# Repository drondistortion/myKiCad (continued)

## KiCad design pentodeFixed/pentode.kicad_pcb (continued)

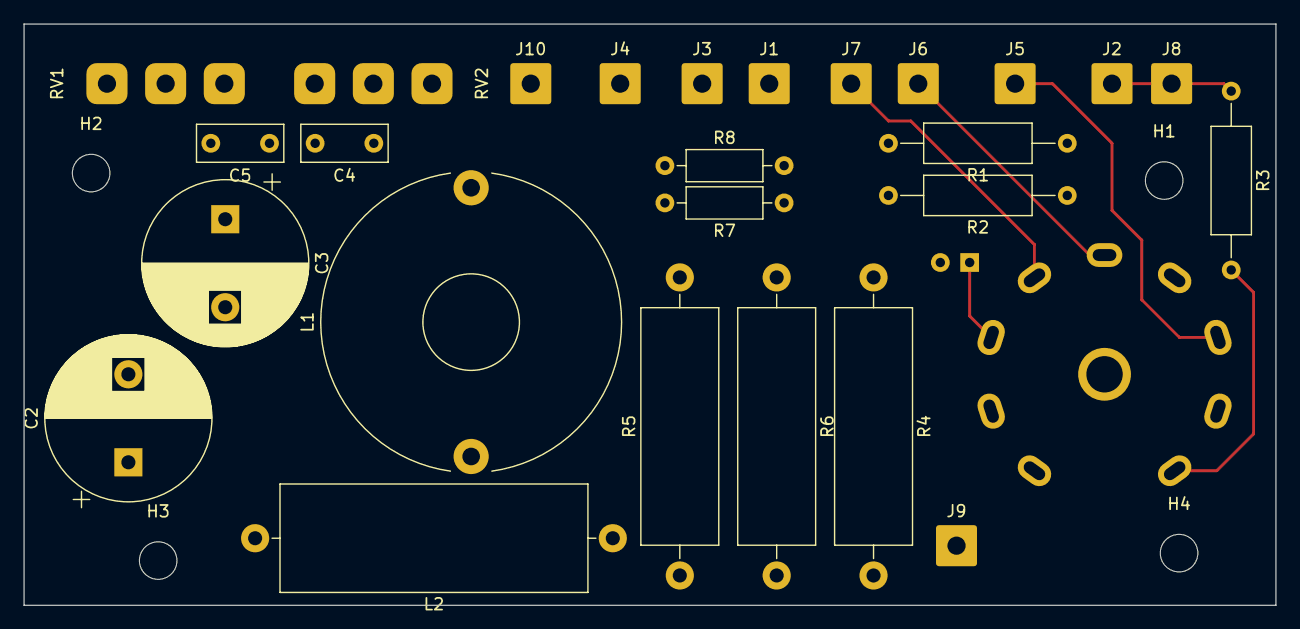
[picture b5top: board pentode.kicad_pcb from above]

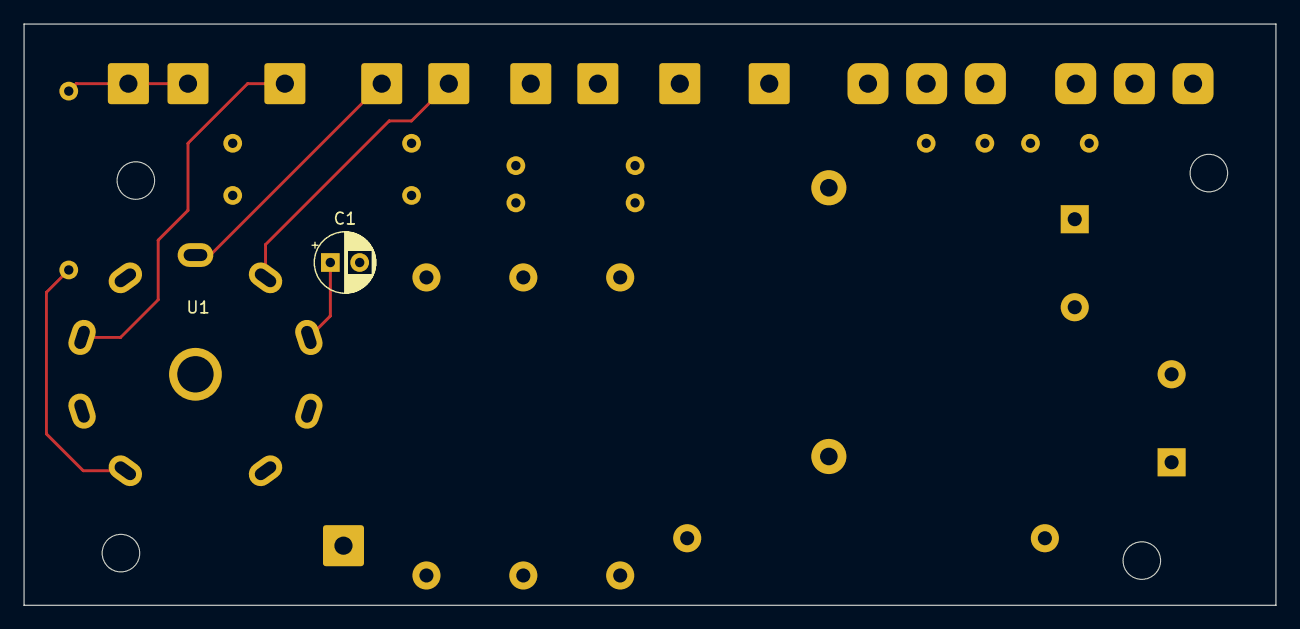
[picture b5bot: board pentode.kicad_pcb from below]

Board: 2 copper layers, 106.7 x 49.5 mm, 32 parts (2 on the bottom side), 15 nets.

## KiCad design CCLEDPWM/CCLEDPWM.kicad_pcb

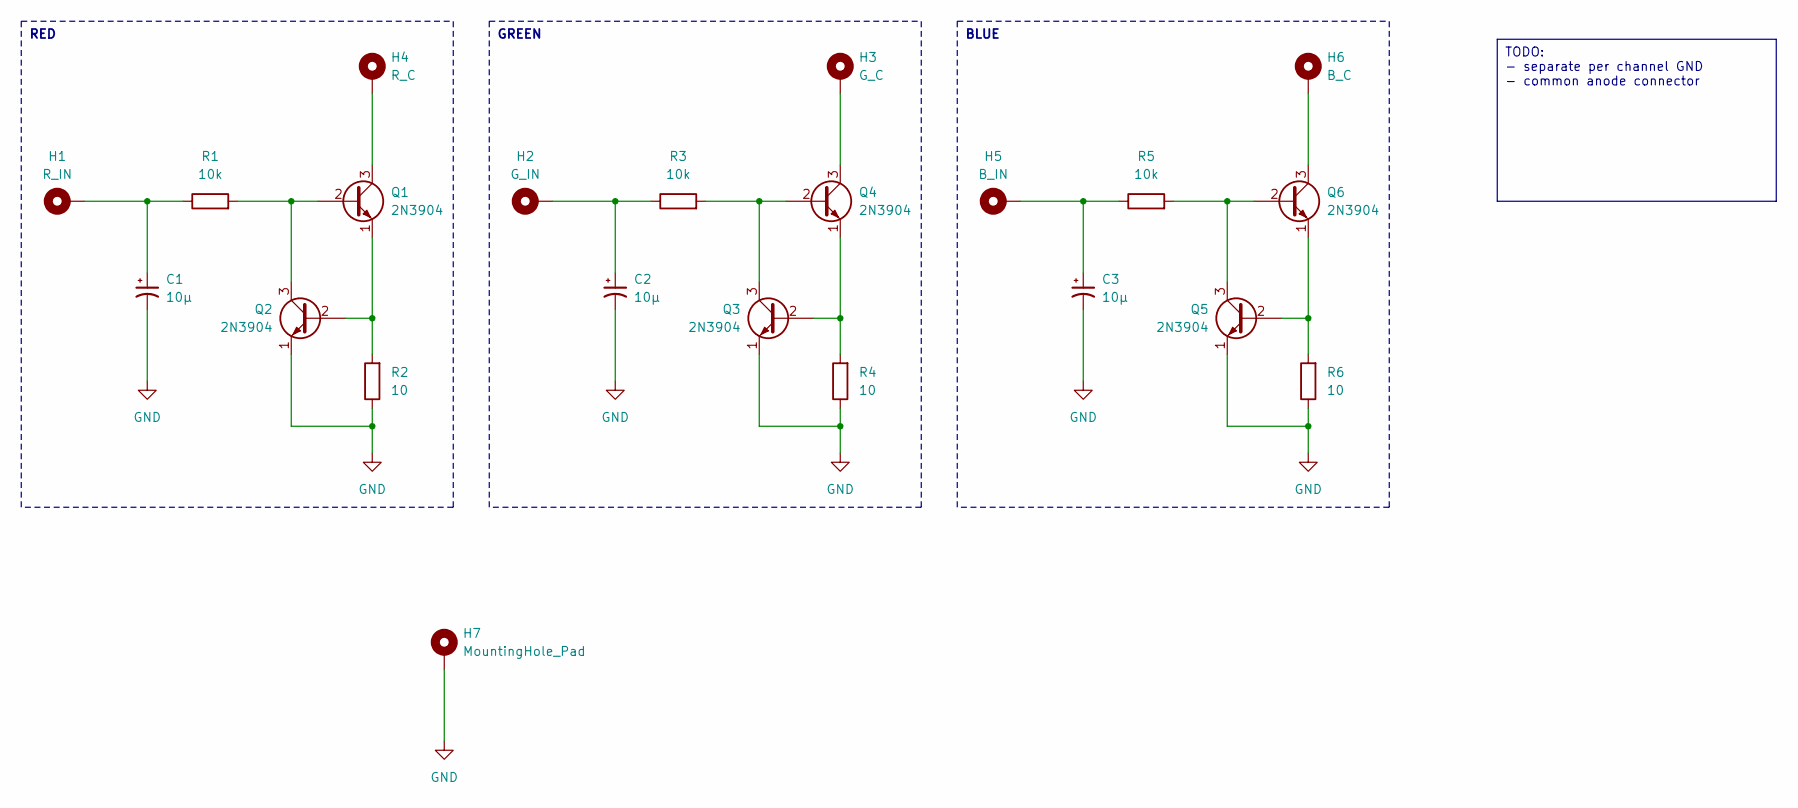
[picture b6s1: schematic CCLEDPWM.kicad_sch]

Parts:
C1, C2, C3: 10µ; CP_Radial_D5.0mm_P2.50mm
H1: R_IN; MountingHole_2.7mm_Pad
H2: G_IN; MountingHole_2.7mm_Pad
H3: G_C; MountingHole_2.7mm_Pad
H4: R_C; MountingHole_2.7mm_Pad
H5: B_IN; MountingHole_2.7mm_Pad
H6: B_C; MountingHole_2.7mm_Pad
H7: MountingHole_Pad; MountingHole_2.7mm_Pad
Q1, Q2, Q3, Q4, Q5, Q6: 2N3904; TO-92_Inline_Wide
R1, R3, R5: 10k; R_Axial_DIN0204_L3.6mm_D1.6mm_P7.62mm_Horizontal
R2, R4, R6: 10; R_Axial_DIN0204_L3.6mm_D1.6mm_P7.62mm_Horizontal

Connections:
GND: C1.2, C2.2, C3.2, H7.1, Q2.1 (E), Q3.1 (E), Q5.1 (E), R2.1, R4.1, R6.1
unnamed: C1.1, H1.1, R1.1
unnamed: C2.1, H2.1, R3.1
unnamed: C3.1, H5.1, R5.1
unnamed: Q1.2 (B), Q2.3 (C), R1.2
unnamed: H4.1, Q1.3 (C)
unnamed: Q1.1 (E), Q2.2 (B), R2.2
unnamed: Q3.2 (B), Q4.1 (E), R4.2
unnamed: Q3.3 (C), Q4.2 (B), R3.2
unnamed: H3.1, Q4.3 (C)
unnamed: Q5.2 (B), Q6.1 (E), R6.2
unnamed: Q5.3 (C), Q6.2 (B), R5.2
unnamed: H6.1, Q6.3 (C)

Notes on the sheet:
TODO: - separate per channel GND - common anode connector
GREEN
BLUE
RED

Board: 2 copper layers, 22 parts (0 on the bottom side), 13 nets, no tracks yet.

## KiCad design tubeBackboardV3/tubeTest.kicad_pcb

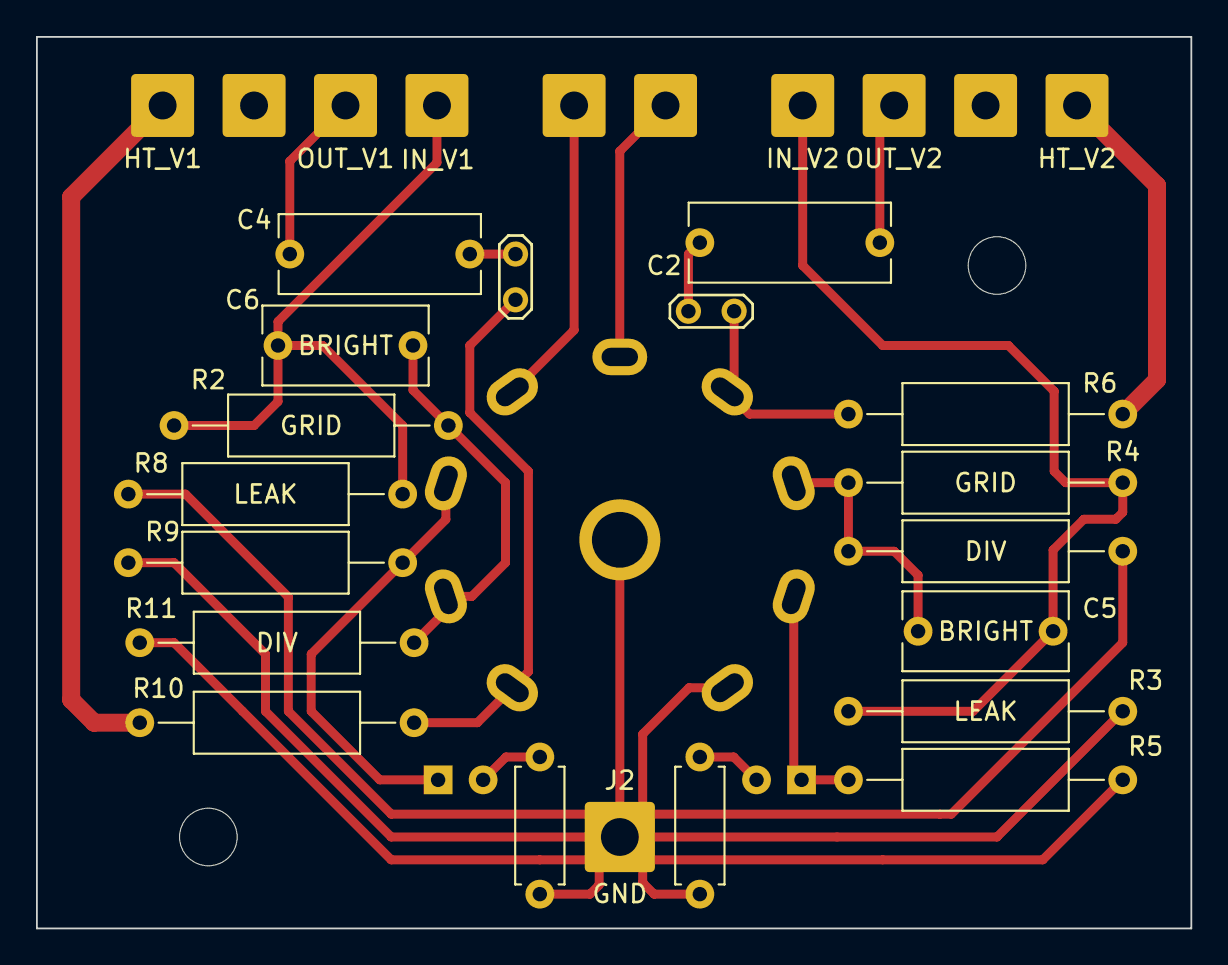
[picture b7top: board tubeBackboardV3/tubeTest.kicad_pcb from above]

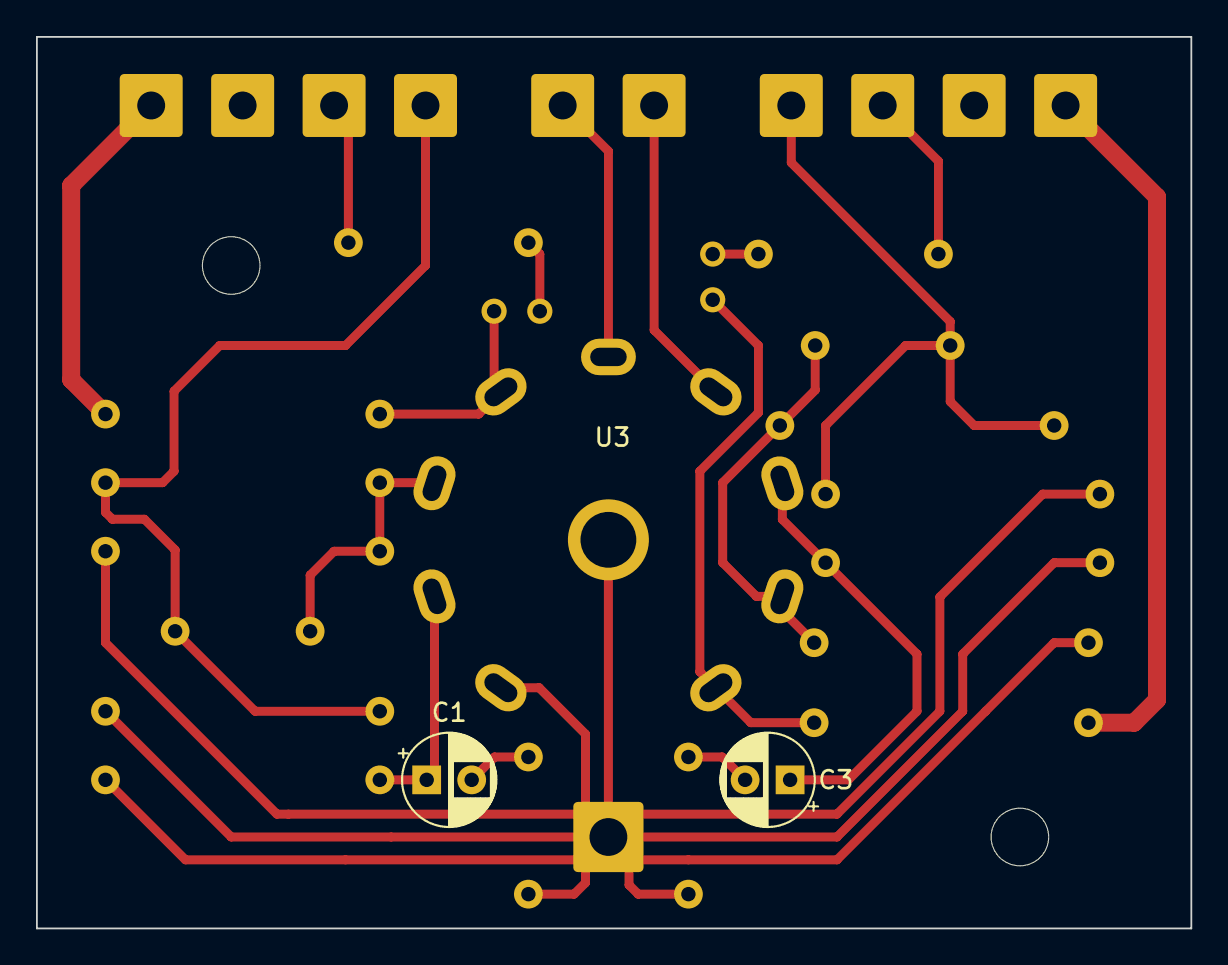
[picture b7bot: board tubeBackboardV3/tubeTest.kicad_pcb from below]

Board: 2 copper layers, 64.1 x 49.5 mm, 34 parts (3 on the bottom side), 19 nets.

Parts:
C1: 0.1µF; CP_Radial_D5.0mm_P2.50mm
C2, C4: 22n; C_Rect_L11.0mm_W4.2mm_P10.00mm_MKT
C3: 1µF; CP_Radial_D5.0mm_P2.50mm
C5, C6: BRIGHT; C_Rect_L9.0mm_W4.2mm_P7.50mm_MKT
H1, H2: MountingHole; MountingHole_3.2mm_M3
J1: IN_V2; SolderWire-0.75sqmm_1x01_D1.25mm_OD3.5mm
J2: GND; SolderWire-1.5sqmm_1x01_D1.7mm_OD3.9mm
J3, J6: ACFIL; SolderWire-0.75sqmm_1x01_D1.25mm_OD3.5mm
J4, J11: BL; SolderWire-0.75sqmm_1x01_D1.25mm_OD3.5mm
J5: OUT_V1; SolderWire-0.75sqmm_1x01_D1.25mm_OD3.5mm
J7: IN_V1; SolderWire-0.75sqmm_1x01_D1.25mm_OD3.5mm
J8: OUT_V2; SolderWire-0.75sqmm_1x01_D1.25mm_OD3.5mm
J9: HT_V2; SolderWire-0.75sqmm_1x01_D1.25mm_OD3.5mm
J10: HT_V1; SolderWire-0.75sqmm_1x01_D1.25mm_OD3.5mm
R1, R11: DIV; R_Axial_DIN0309_L9.0mm_D3.2mm_P15.24mm_Horizontal
R2, R4: GRID; R_Axial_DIN0309_L9.0mm_D3.2mm_P15.24mm_Horizontal
R3, R8: LEAK; R_Axial_DIN0309_L9.0mm_D3.2mm_P15.24mm_Horizontal
R5, R9: 1.8K; R_Axial_DIN0309_L9.0mm_D3.2mm_P15.24mm_Horizontal
R6, R10: 220K; R_Axial_DIN0309_L9.0mm_D3.2mm_P15.24mm_Horizontal
R7, R12: 100; R_Axial_DIN0207_L6.3mm_D2.5mm_P7.62mm_Horizontal
TP3, TP4: TestPoint_2Pole; TestPoint_2Pads_Pitch2.54mm_Drill0.8mm
U3: ECC83; Valve_6N2P

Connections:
+3V0: J6.1, U3.5 (F1)
-3V3: J3.1, U3.4 (F1)
GND: J2.1, R1.1, R3.2, R5.2, R7.2, R8.1, R9.2, R11.1, R12.2, U3.9 (F2)
unnamed: C1.2, R7.1
unnamed: C2.1, TP3.1
unnamed: C3.2, R12.1
unnamed: C4.1, TP4.1
unnamed: C5.1, J1.1, R3.1, R4.1
unnamed: C4.2, J5.1
unnamed: C6.1, J7.1, R2.1, R8.2
unnamed: C2.2, J8.1
unnamed: J9.1, R6.1
unnamed: J10.1, R10.1
unnamed: R6.2, TP3.2, U3.6 (A)
unnamed: C5.2, R1.2, R4.2, U3.7 (G)
unnamed: C1.1, R5.1, U3.8 (K)
unnamed: R10.2, TP4.2, U3.1 (A)
unnamed: C6.2, R2.2, R11.2, U3.2 (G)
unnamed: C3.1, R9.1, U3.3 (K)

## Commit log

2025-01-25 bleh
2025-02-03 tube ressurection
2025-04-03 kicad 9.0
2025-04-06 gravity with supply
2025-05-05 pre mark II soldering
2025-05-13 pre actual tonestack
2025-06-03 Ornex Z-lock
2025-06-05 almost...
2025-06-06 bat mon done
2025-06-09 fucked up
2025-06-11 ornex lock pcb
2025-06-11 half done
2025-06-12 doesn't fit...
2025-06-12 rethinking
2025-06-12 esp placed
2025-06-12 unlock
2025-06-12 pre traces
2025-06-13 gate swaps...
2025-06-15 frootloop day dream...
2025-06-15 rf begins...
